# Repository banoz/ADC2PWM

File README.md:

The board can be used as a 0-5V voltage input to PWM output adapter.

J1 matches popular flow meter connectors.

Supply voltage is 12V. For 5V supply IC1 must be replaced with a diode/shunt.

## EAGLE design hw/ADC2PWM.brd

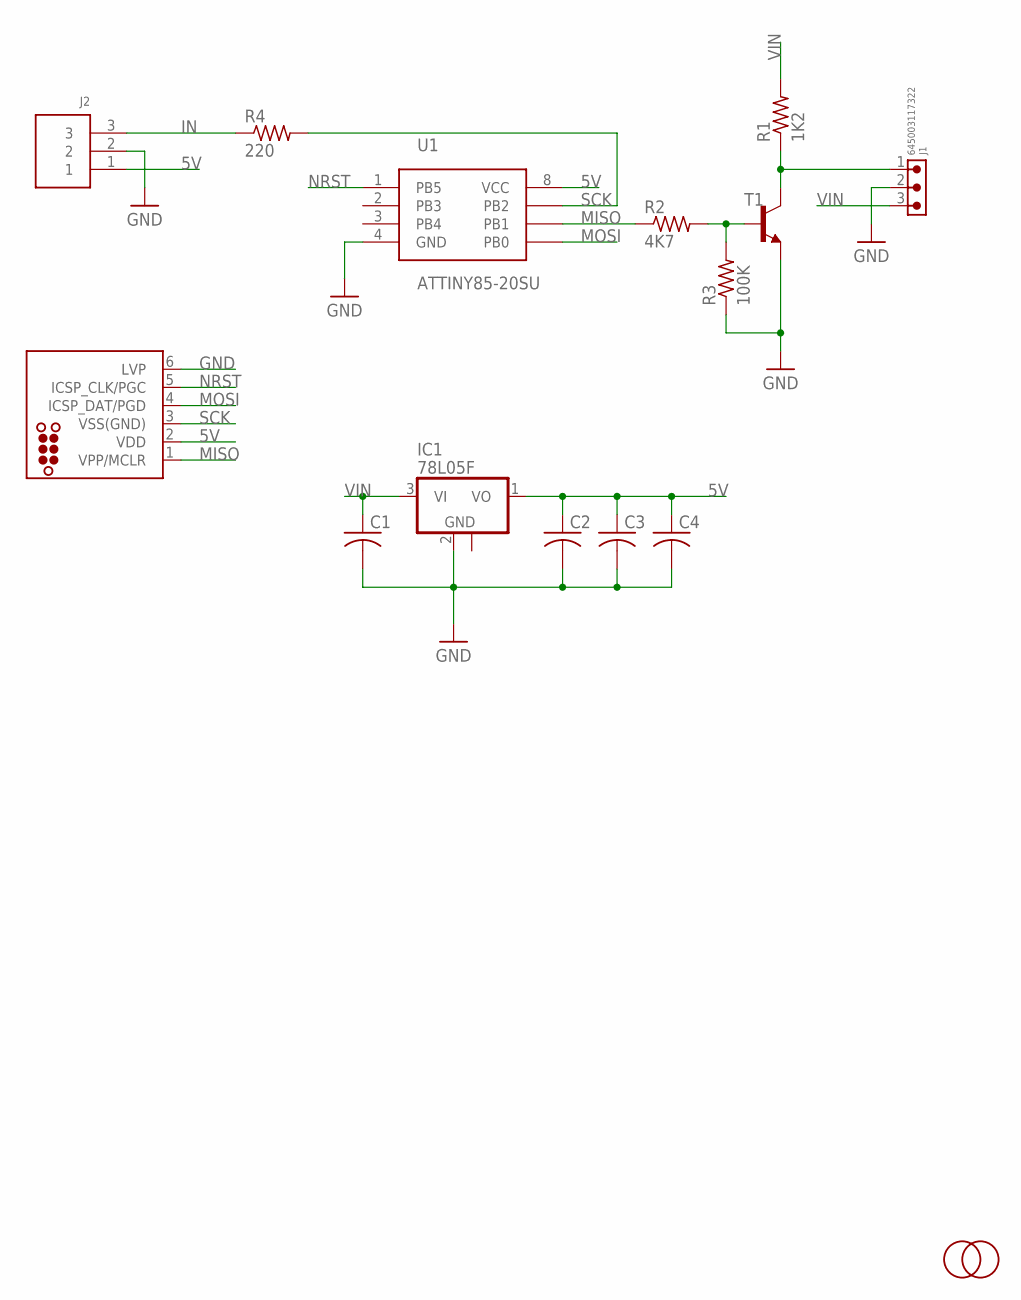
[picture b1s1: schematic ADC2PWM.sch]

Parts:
C1, C2, C3, C4: C-USC0603; C0603
IC1: 78L05F; SOT89
J1: 645003117322
J2: 3PIN; B3B-PH-K-S
J3: TC2030-MCP-NL
R1: 1K2; R0603
R2: 4K7; R0603
R3: 100K; R0603
R4: 220; R0603
T1: MMBT2222ALT1-NPN-SOT23-BEC; SOT23-BEC
U1: ATTINY85-20SU; SOIC-8
U$1, U$2: FIDUCIAL; FIDUCIAL_1MM

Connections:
5V: C2.1, C3.1, C4.1, IC1.1 (VO), J2.1, J3.2 (VDD), U1.8 (VCC)
GND: C1.2, C2.2, C3.2, C4.2, IC1.2 (GND), J1.2, J2.2, J3.6 (LVP), R3.1, T1.E, U1.4 (GND)
IN: J2.3, R4.1
MISO: J3.1 (VPP/MCLR), R2.1, U1.6 (PB1)
MOSI: J3.4 (ICSP_DAT/PGD), U1.5 (PB0)
unnamed: J1.1, R1.1, T1.C
unnamed: R2.2, R3.2, T1.B
NRST: J3.5 (ICSP_CLK/PGC), U1.1 (PB5)
SCK: J3.3 (VSS(GND)), R4.2, U1.7 (PB2)
VIN: C1.1, IC1.3 (VI), J1.3, R1.2

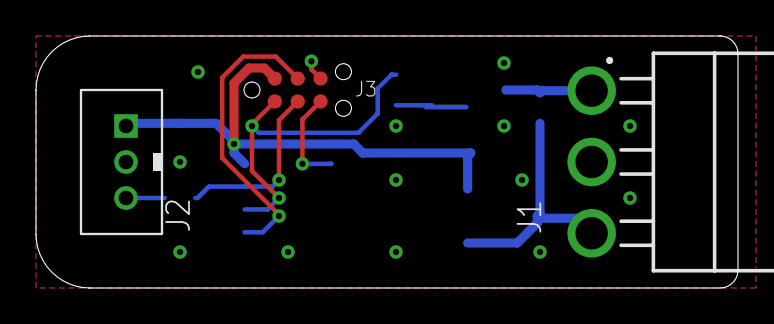
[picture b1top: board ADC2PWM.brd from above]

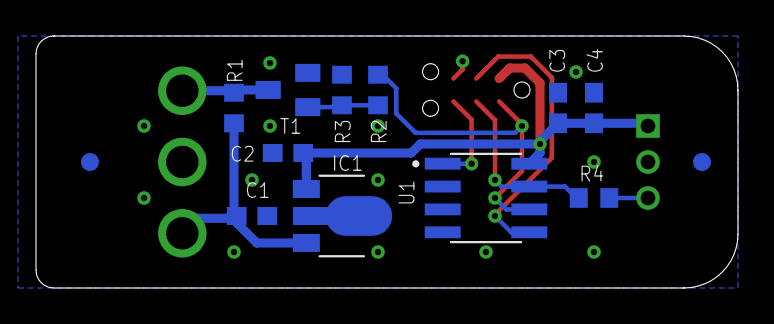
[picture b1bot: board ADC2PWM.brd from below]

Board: 2 copper layers, 39.0 x 14.0 mm, 16 parts (13 on the bottom side), 10 nets.

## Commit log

2024-09-27 Initial code commit
2024-09-27 Initial HW commit
2026-02-22 Update README with board usage details
2026-02-22 WDT + signal inverse

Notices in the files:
hw/ADC2PWM.brd:
ADC2PWM ©Vas
parts and their libraries:
Wurth_Connectors_WR-WTB: Copyright: Würth Elektronik
tag-connect: ©2009 ROFA.cz - modified and updated by Robert Darlington ‹rdarlington@gmail.com›
